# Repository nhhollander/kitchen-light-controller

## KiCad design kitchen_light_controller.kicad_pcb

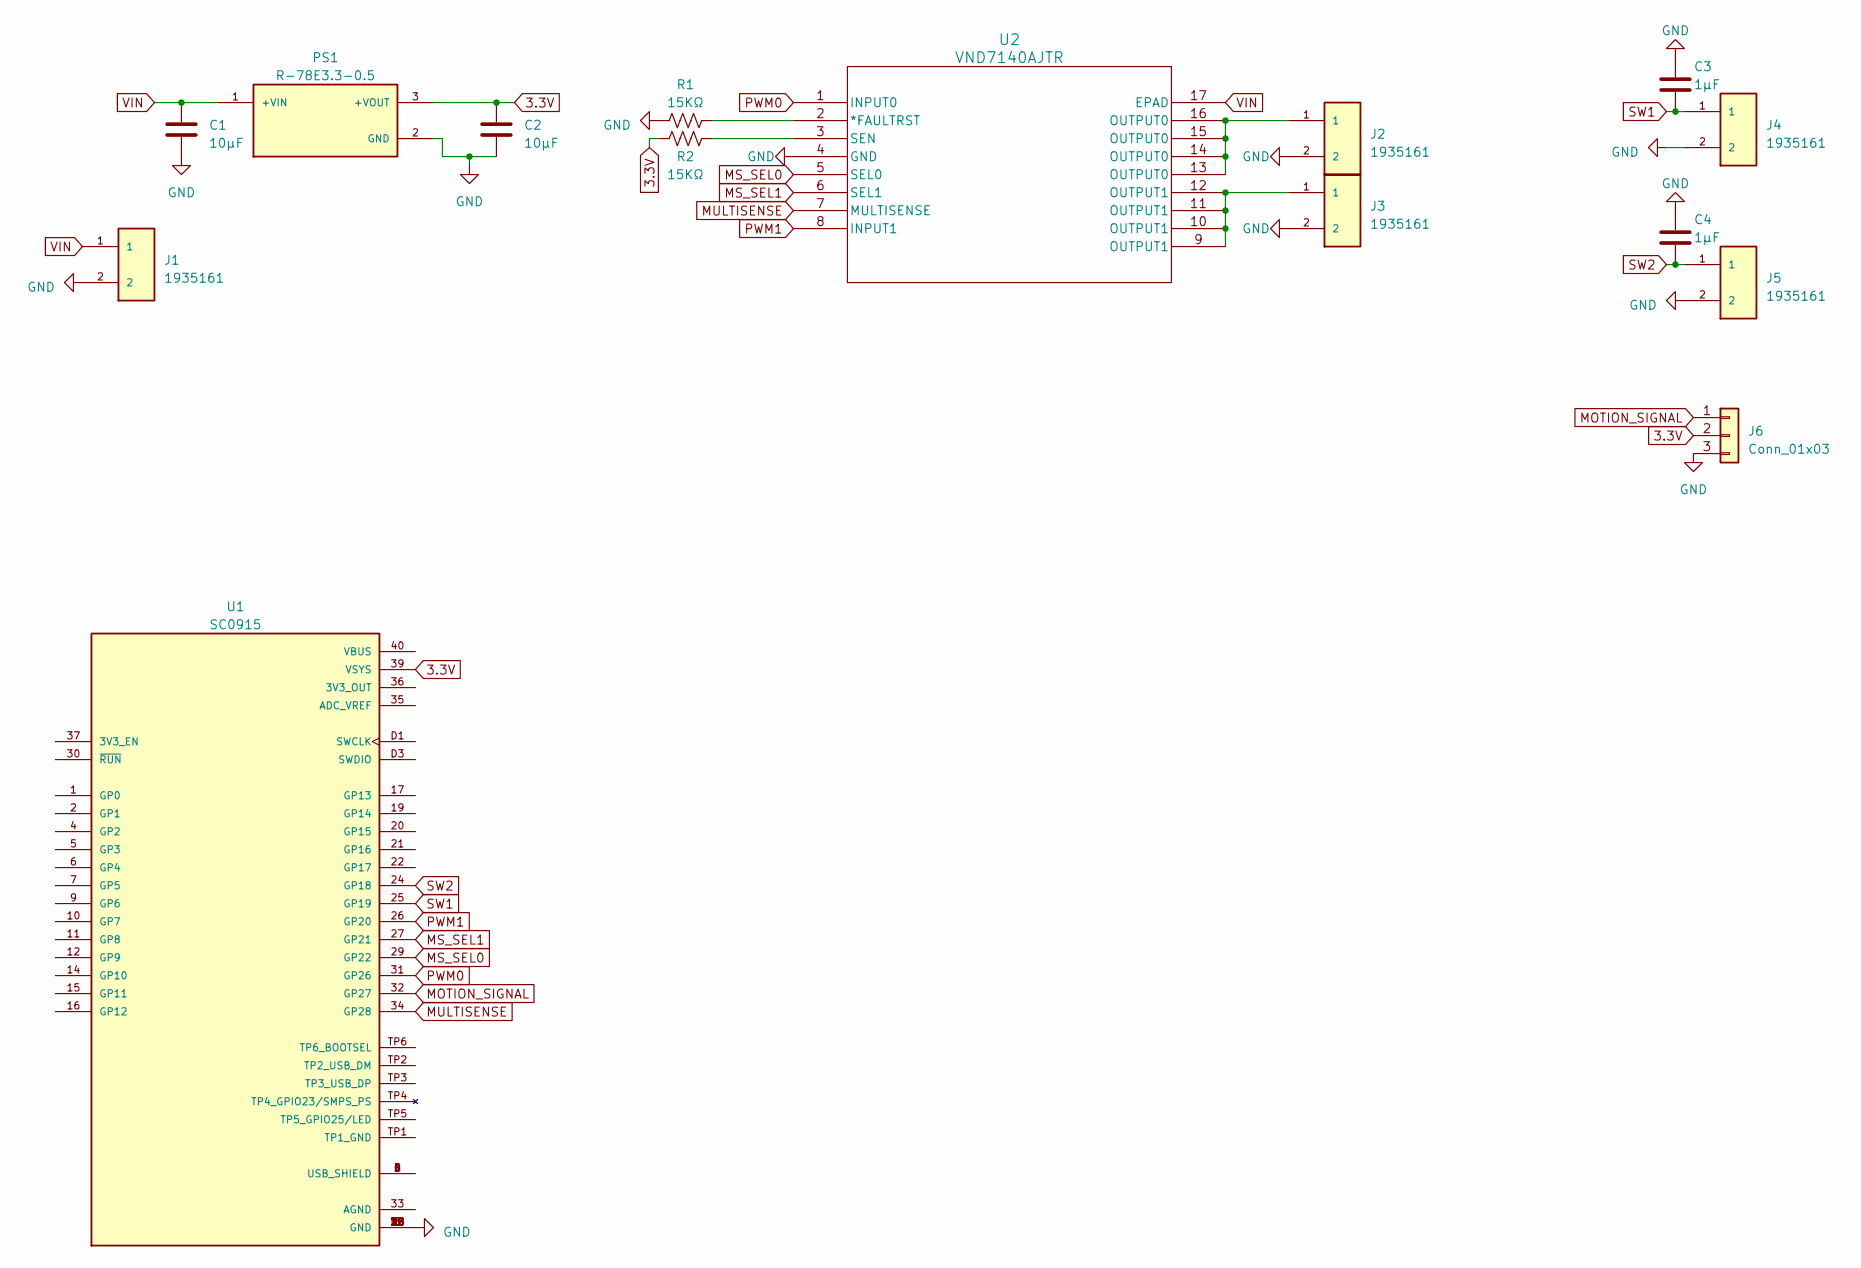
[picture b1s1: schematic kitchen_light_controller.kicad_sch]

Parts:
C1, C2: 10μF; C_0805_2012Metric_Pad1.18x1.45mm_HandSolder
C3, C4: 1μF; C_0805_2012Metric_Pad1.18x1.45mm_HandSolder
J1, J2, J3, J4, J5: 1935161; PHOENIX_1935161
J6: Conn_01x03; PinHeader_1x03_P2.54mm_Vertical
PS1: R-78E3.3-0.5; CONV_R-78E3.3-0.5; PARTREV 4
R1, R2: 15KΩ; R_0201_0603Metric_Pad0.64x0.40mm_HandSolder
U1: SC0915; MODULE_SC0915; PARTREV 1.9
U2: VND7140AJTR; POWERSSO16_STM

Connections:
3.3V: C2.1, J6.2, PS1.3 (+VOUT), R2.1, U1.39 (VSYS)
GND: C1.2, C2.2, C3.1, C4.1, J1.2, J2.2, J3.2, J4.2, J5.2, J6.3, PS1.2 (GND), R1.1, U1.3 (GND), U1.8 (GND), U1.13 (GND), U1.18 (GND), U1.23 (GND), U1.28 (GND), U1.38 (GND), U1.D2 (GND), U2.4 (GND)
MOTION_SIGNAL: J6.1, U1.32 (GP27)
MS_SEL0: U1.29 (GP22), U2.5 (SEL0)
MS_SEL1: U1.27 (GP21), U2.6 (SEL1)
MULTISENSE: U1.34 (GP28), U2.7 (MULTISENSE)
unnamed: J2.1, U2.13 (OUTPUT0), U2.14 (OUTPUT0), U2.15 (OUTPUT0), U2.16 (OUTPUT0)
unnamed: J3.1, U2.9 (OUTPUT1), U2.10 (OUTPUT1), U2.11 (OUTPUT1), U2.12 (OUTPUT1)
unnamed: U1.A (USB_SHIELD), U1.B (USB_SHIELD), U1.C (USB_SHIELD), U1.D (USB_SHIELD)
unnamed: R1.2, U2.2 (*FAULTRST)
unnamed: R2.2, U2.3 (SEN)
PWM0: U1.31 (GP26), U2.1 (INPUT0)
PWM1: U1.26 (GP20), U2.8 (INPUT1)
SW1: C3.2, J4.1, U1.25 (GP19)
SW2: C4.2, J5.1, U1.24 (GP18)
VIN: C1.1, J1.1, PS1.1 (+VIN), U2.17 (EPAD)

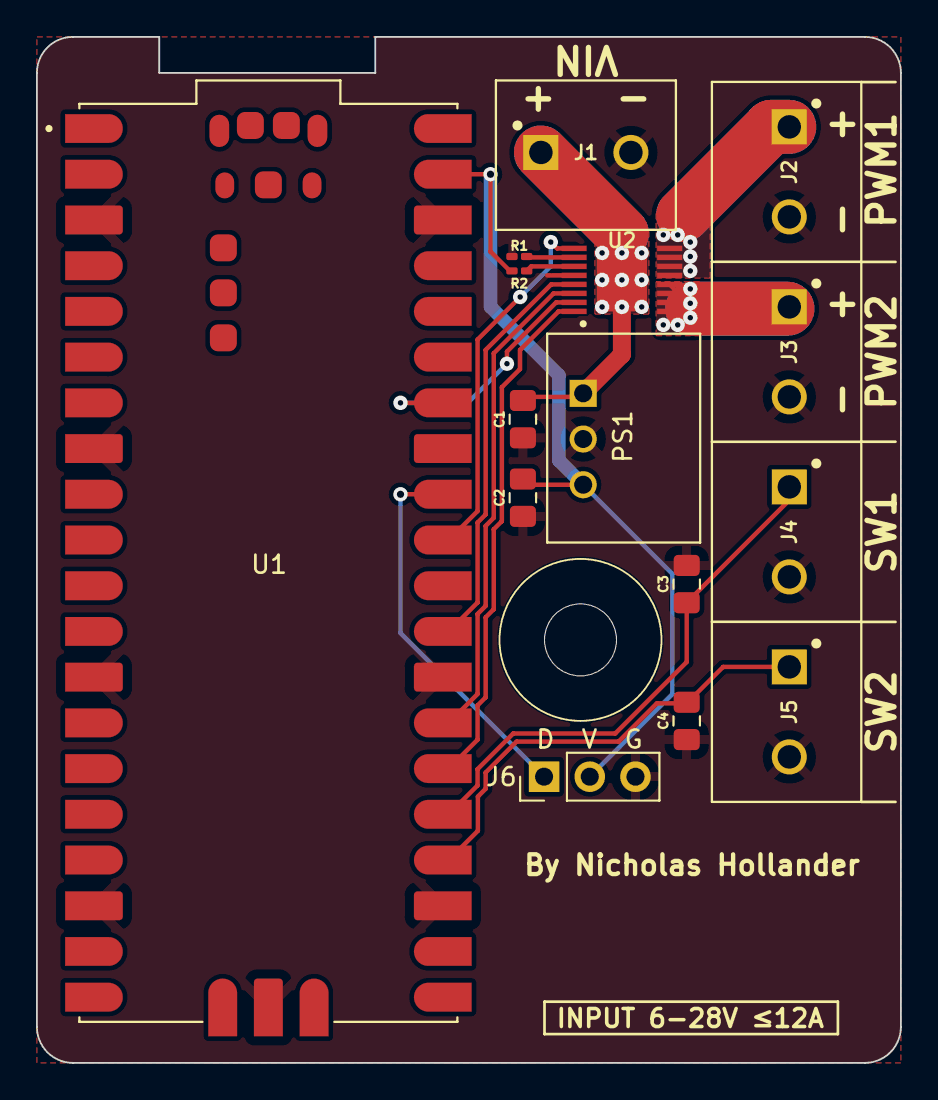
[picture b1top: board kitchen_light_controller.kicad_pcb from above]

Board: 2 copper layers, 48.0 x 57.0 mm, 15 parts (0 on the bottom side), 16 nets.

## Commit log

2023-04-23 Reduced to dual channel (Single IC)
2023-04-23 Reinforced current carrying traces with vias
2023-04-23 Added debounced control switches
2023-04-24 Added analog motion sensor header
2023-04-24 Revision 1.0
2023-04-24 Added readme
